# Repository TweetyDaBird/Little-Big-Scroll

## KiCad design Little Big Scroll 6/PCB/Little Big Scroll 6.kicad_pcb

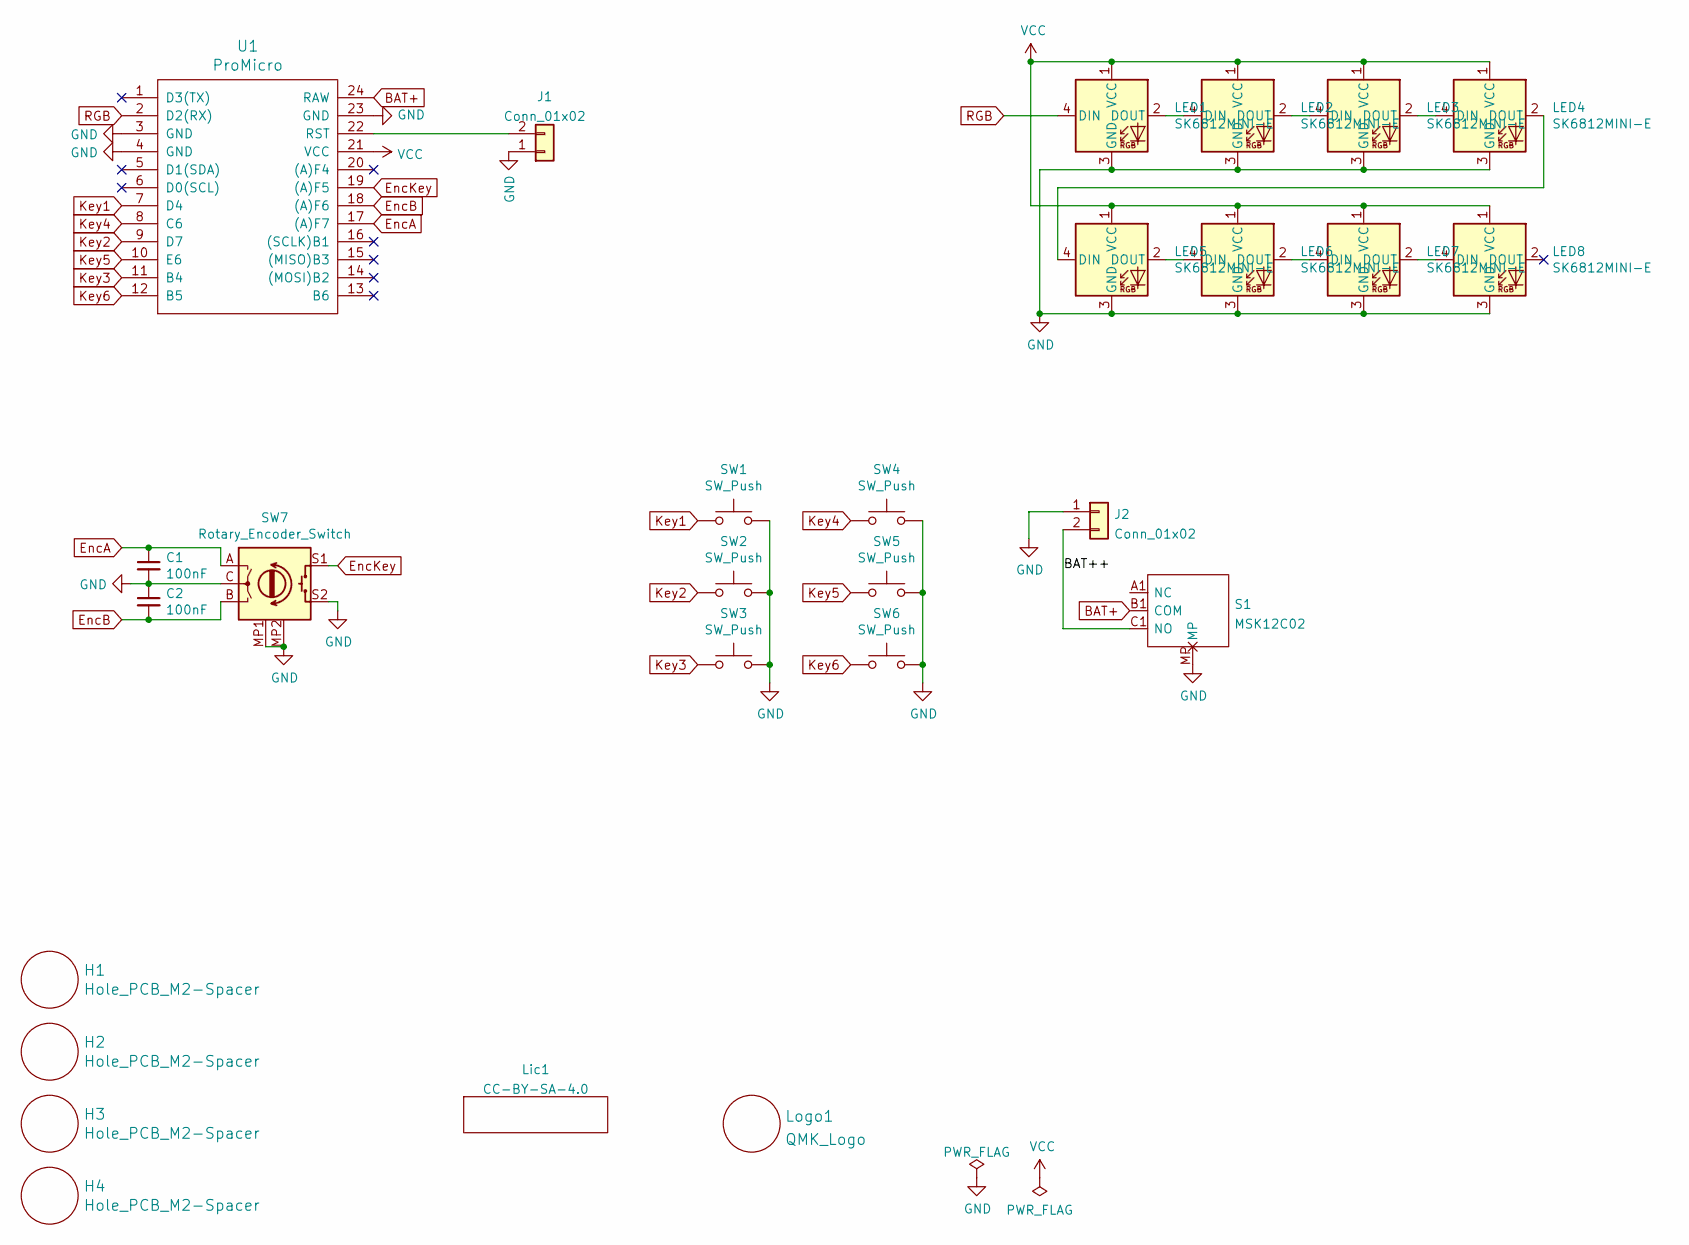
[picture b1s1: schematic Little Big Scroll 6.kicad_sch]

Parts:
C1, C2: 100nF; C_Axial_L3.8mm_D2.6mm_P7.50mm_Horizontal
H1, H2, H3, H4: Hole_PCB_M2-Spacer; MountingHole_3.7mm
J1: Conn_01x02; PinHeader_1x02_P2.54mm_Vertical
J2: Conn_01x02; JST_PH_S2B-PH-K_1x02_P2.00mm_Horizontal
LED1, LED2, LED3, LED4, LED5, LED6, LED7, LED8: SK6812MINI-E; MX_SK6812MINI-E
Lic1: CC-BY-SA-4.0; CC_BY_SA_40
Logo1: QMK_Logo; Powered_by_QMK
S1: MSK12C02; Manufacturer_Part_Number MSK12C02
SW1, SW2, SW3, SW4, SW5, SW6: SW_Push; Kailh_socket_MX_RGB
SW7: Rotary_Encoder_Switch; RotaryEncoder_Alps_EC11E-Switch_Vertical_H20mm
U1: ProMicro; ArduinoProMicro

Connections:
/BAT++: J2.2, S1.C1 (NO)
BAT+: S1.B1 (COM), U1.24 (RAW)
EncA: C1.1, SW7.A, U1.17 ((A)F7)
EncB: C2.2, SW7.B, U1.18 ((A)F6)
EncKey: SW7.S1, U1.19 ((A)F5)
GND: C1.2, C2.1, J1.1, J2.1, LED1.3 (GND), LED2.3 (GND), LED3.3 (GND), LED4.3 (GND), LED5.3 (GND), LED6.3 (GND), LED7.3 (GND), LED8.3 (GND), S1.MP, SW1.1, SW2.1, SW3.1, SW4.1, SW5.1, SW6.1, SW7.C, SW7.MP1 (GND), SW7.MP2 (GND), SW7.S2, U1.3 (GND), U1.4 (GND), U1.23 (GND)
Key1: SW1.2, U1.7 (D4)
Key2: SW2.2, U1.9 (D7)
Key3: SW3.2, U1.11 (B4)
Key4: SW4.2, U1.8 (C6)
Key5: SW5.2, U1.10 (E6)
Key6: SW6.2, U1.12 (B5)
unnamed: J1.2, U1.22 (RST)
unnamed: LED1.2 (DOUT), LED2.4 (DIN)
unnamed: LED2.2 (DOUT), LED3.4 (DIN)
unnamed: LED3.2 (DOUT), LED4.4 (DIN)
unnamed: LED4.2 (DOUT), LED5.4 (DIN)
unnamed: LED5.2 (DOUT), LED6.4 (DIN)
unnamed: LED6.2 (DOUT), LED7.4 (DIN)
unnamed: LED7.2 (DOUT), LED8.4 (DIN)
RGB: LED1.4 (DIN), U1.2 (D2(RX))
VCC: LED1.1 (VCC), LED2.1 (VCC), LED3.1 (VCC), LED4.1 (VCC), LED5.1 (VCC), LED6.1 (VCC), LED7.1 (VCC), LED8.1 (VCC), U1.21 (VCC)

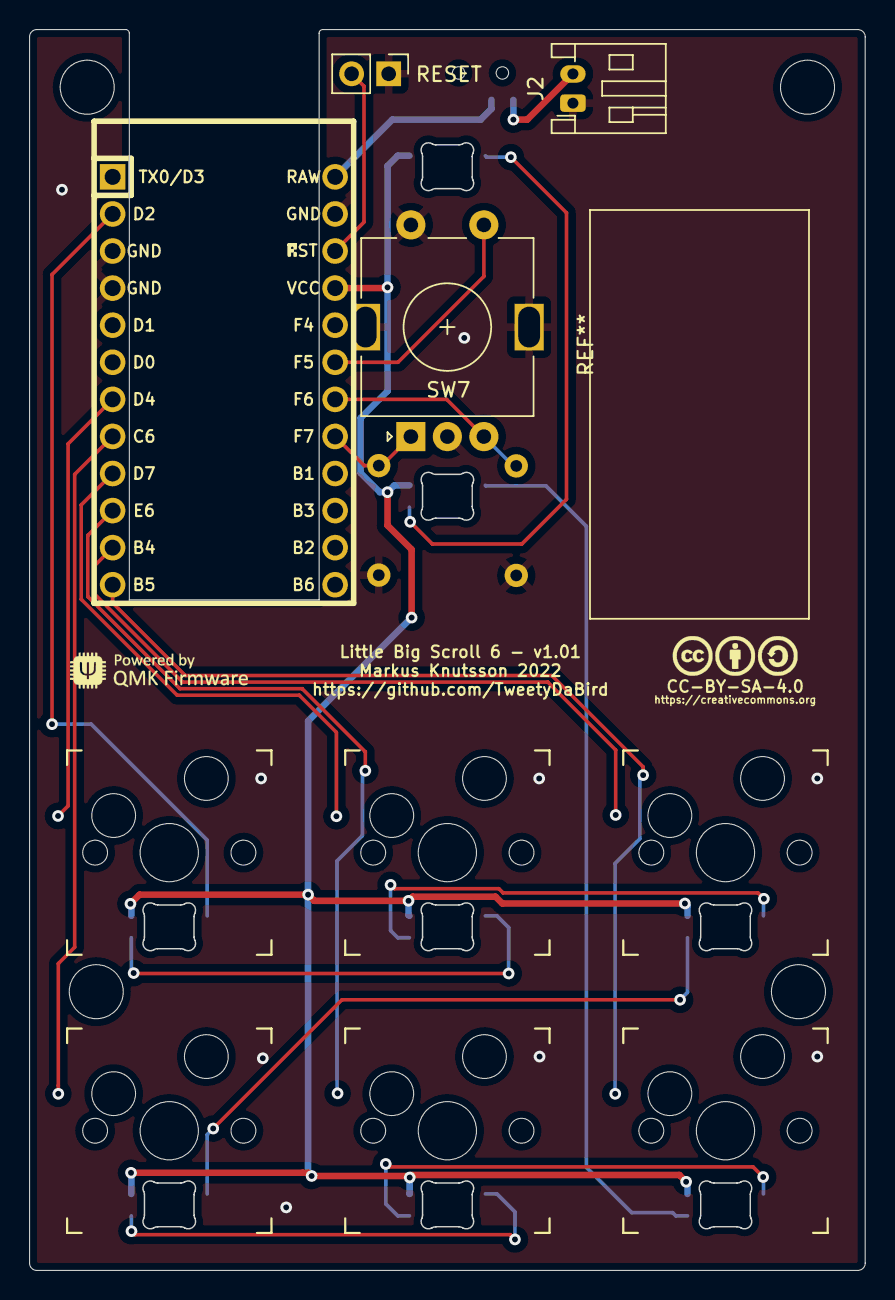
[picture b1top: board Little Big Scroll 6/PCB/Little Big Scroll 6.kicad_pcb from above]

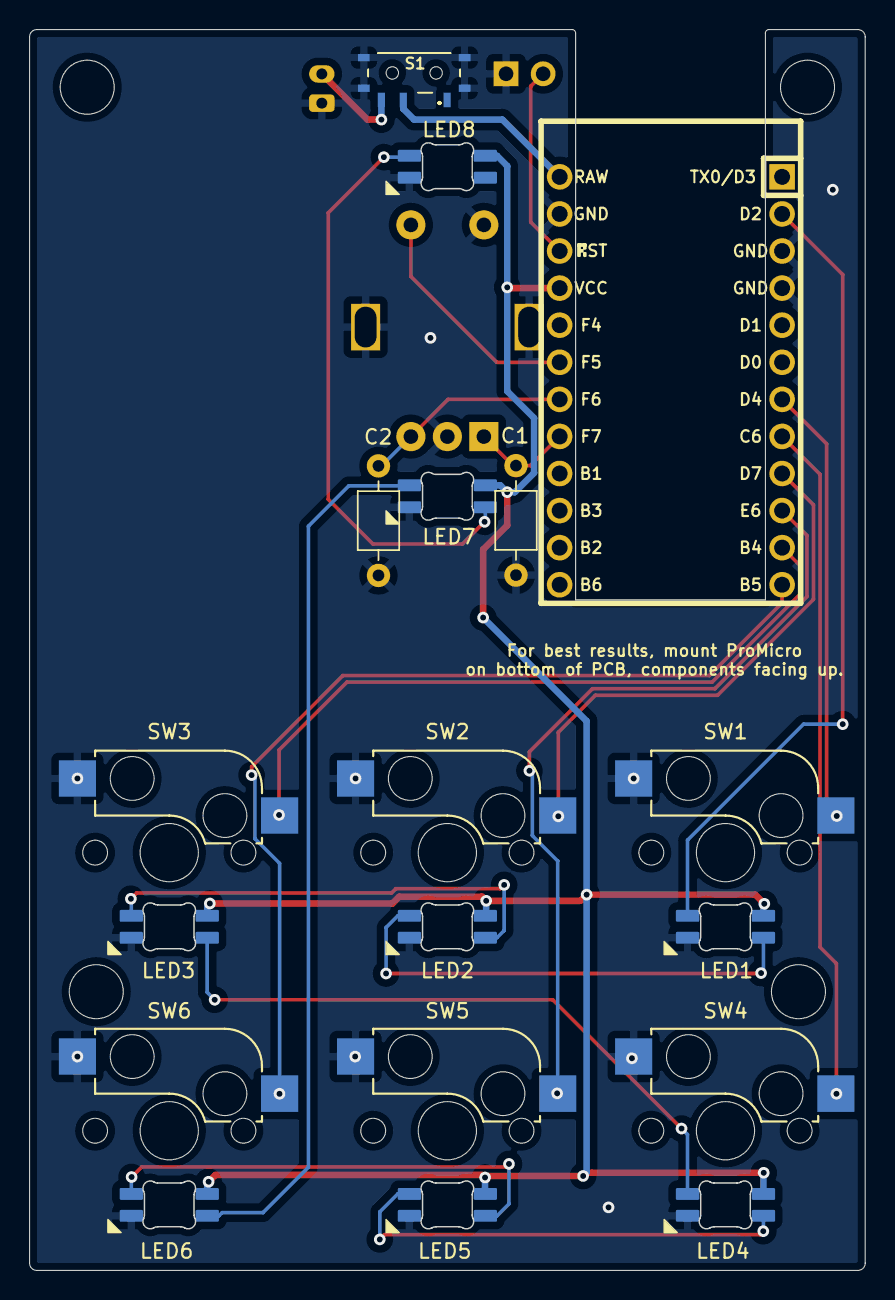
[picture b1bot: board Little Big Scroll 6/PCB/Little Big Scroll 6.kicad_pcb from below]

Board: 2 copper layers, 57.2 x 85.0 mm, 27 parts (3 on the bottom side), 22 nets.

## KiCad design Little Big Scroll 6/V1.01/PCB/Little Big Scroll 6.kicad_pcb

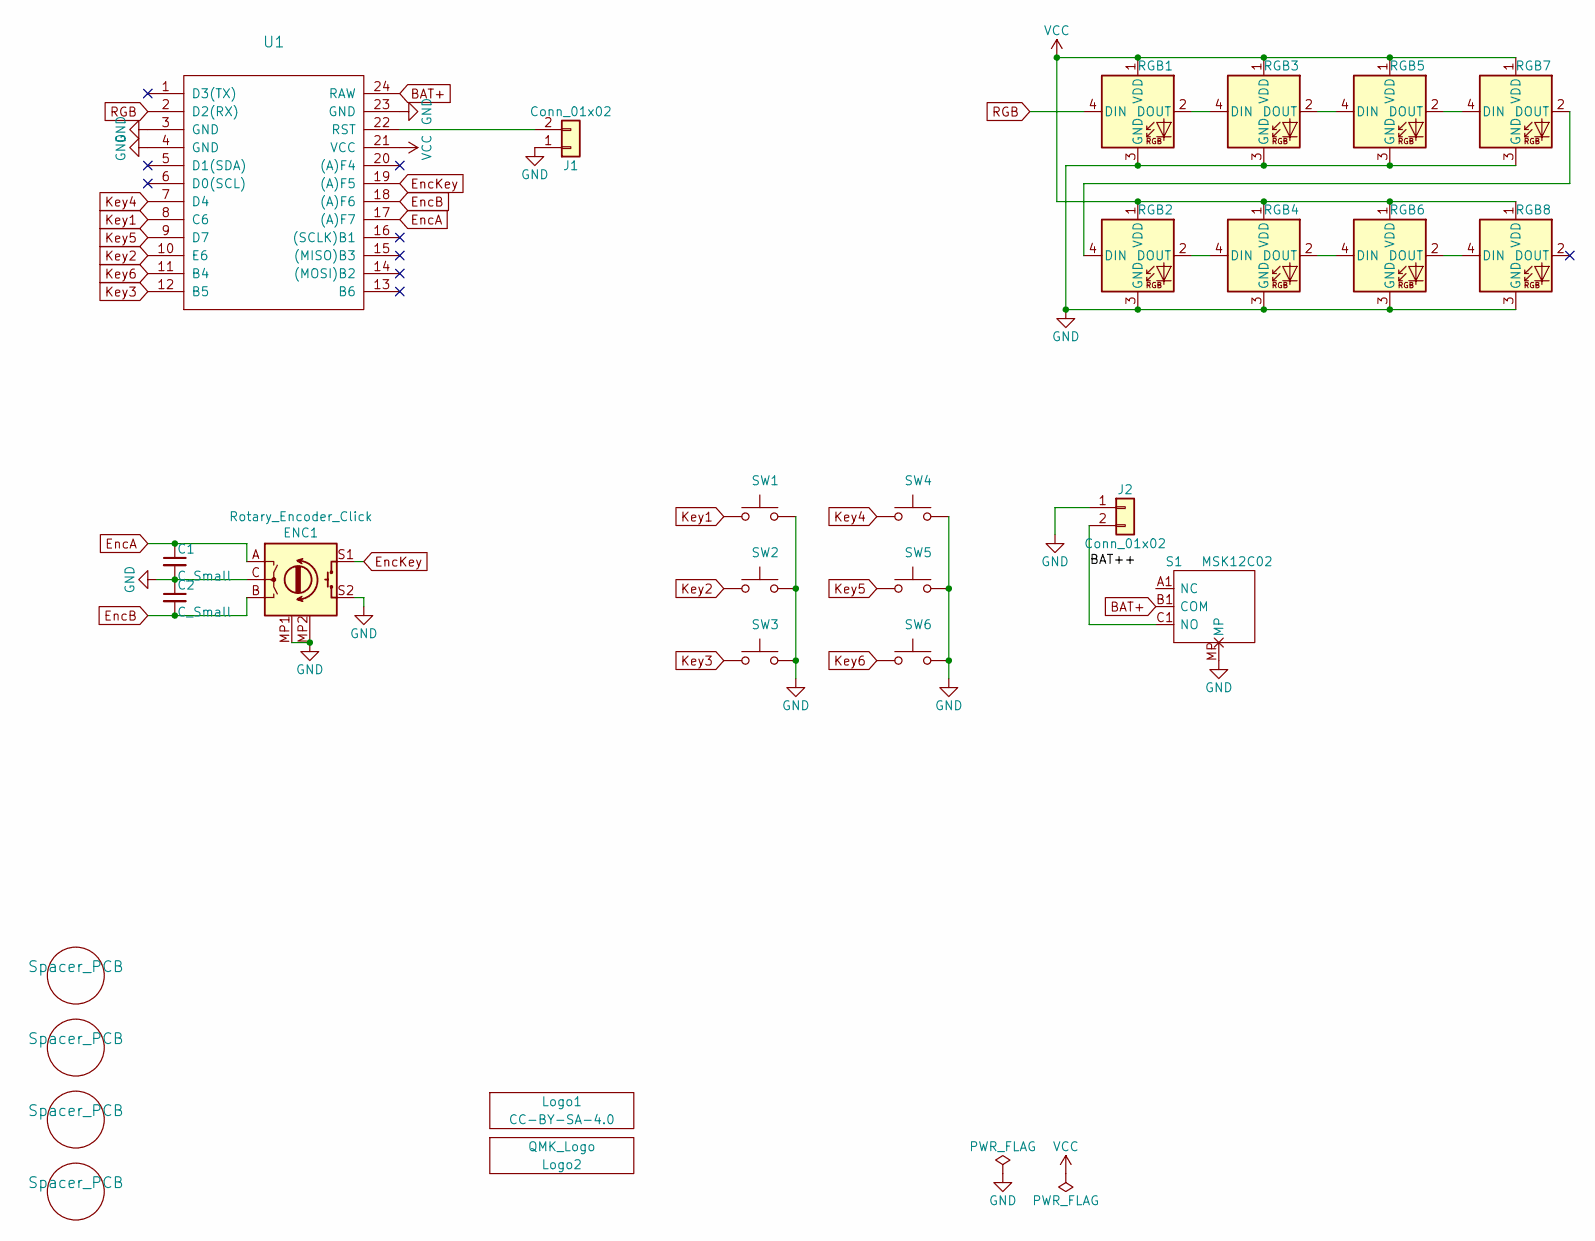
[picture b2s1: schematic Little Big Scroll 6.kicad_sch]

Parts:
C1, C2: C_Small
ENC1: Rotary_Encoder_Click; Encoder_Alps_EC11E
H1, H2, H3, H4: Spacer_PCB; Spacer PCB hole
J1, J2: Conn_01x02
Logo1: CC-BY-SA-4.0; CC_BY_SA_40
Logo2: QMK_Logo; Powered_by_QMK
RGB1, RGB2, RGB3, RGB4, RGB5, RGB6, RGB7, RGB8: SK6812MINI-E; RGB_SK6812MINI-E
S1: MSK12C02; Manufacturer_Part_Number MSK12C02
SW1, SW2, SW3, SW4, SW5, SW6: SW_MX_HS; SW_MX_HotSwap
U1: (no value)

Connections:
/BAT++: J2.2, S1.C1 (NO)
BAT+: S1.B1 (COM), U1.24 (RAW)
EncA: C1.1, ENC1.A, U1.17 ((A)F7)
EncB: C2.2, ENC1.B, U1.18 ((A)F6)
EncKey: ENC1.S1, U1.19 ((A)F5)
GND: C1.2, C2.1, ENC1.C, ENC1.MP1 (GND), ENC1.MP2 (GND), ENC1.S2, J1.1, J2.1, RGB1.3 (GND), RGB2.3 (GND), RGB3.3 (GND), RGB4.3 (GND), RGB5.3 (GND), RGB6.3 (GND), RGB7.3 (GND), RGB8.3 (GND), S1.MP, SW1.2, SW2.2, SW3.2, SW4.2, SW5.2, SW6.2, U1.3 (GND), U1.4 (GND), U1.23 (GND)
Key1: SW1.1, U1.8 (C6)
Key2: SW2.1, U1.10 (E6)
Key3: SW3.1, U1.12 (B5)
Key4: SW4.1, U1.7 (D4)
Key5: SW5.1, U1.9 (D7)
Key6: SW6.1, U1.11 (B4)
unnamed: RGB1.2 (DOUT), RGB3.4 (DIN)
unnamed: RGB2.2 (DOUT), RGB4.4 (DIN)
unnamed: RGB2.4 (DIN), RGB7.2 (DOUT)
unnamed: RGB3.2 (DOUT), RGB5.4 (DIN)
unnamed: RGB4.2 (DOUT), RGB6.4 (DIN)
unnamed: RGB5.2 (DOUT), RGB7.4 (DIN)
unnamed: RGB6.2 (DOUT), RGB8.4 (DIN)
unnamed: J1.2, U1.22 (RST)
RGB: RGB1.4 (DIN), U1.2 (D2(RX))
VCC: RGB1.1 (VDD), RGB2.1 (VDD), RGB3.1 (VDD), RGB4.1 (VDD), RGB5.1 (VDD), RGB6.1 (VDD), RGB7.1 (VDD), RGB8.1 (VDD), U1.21 (VCC)

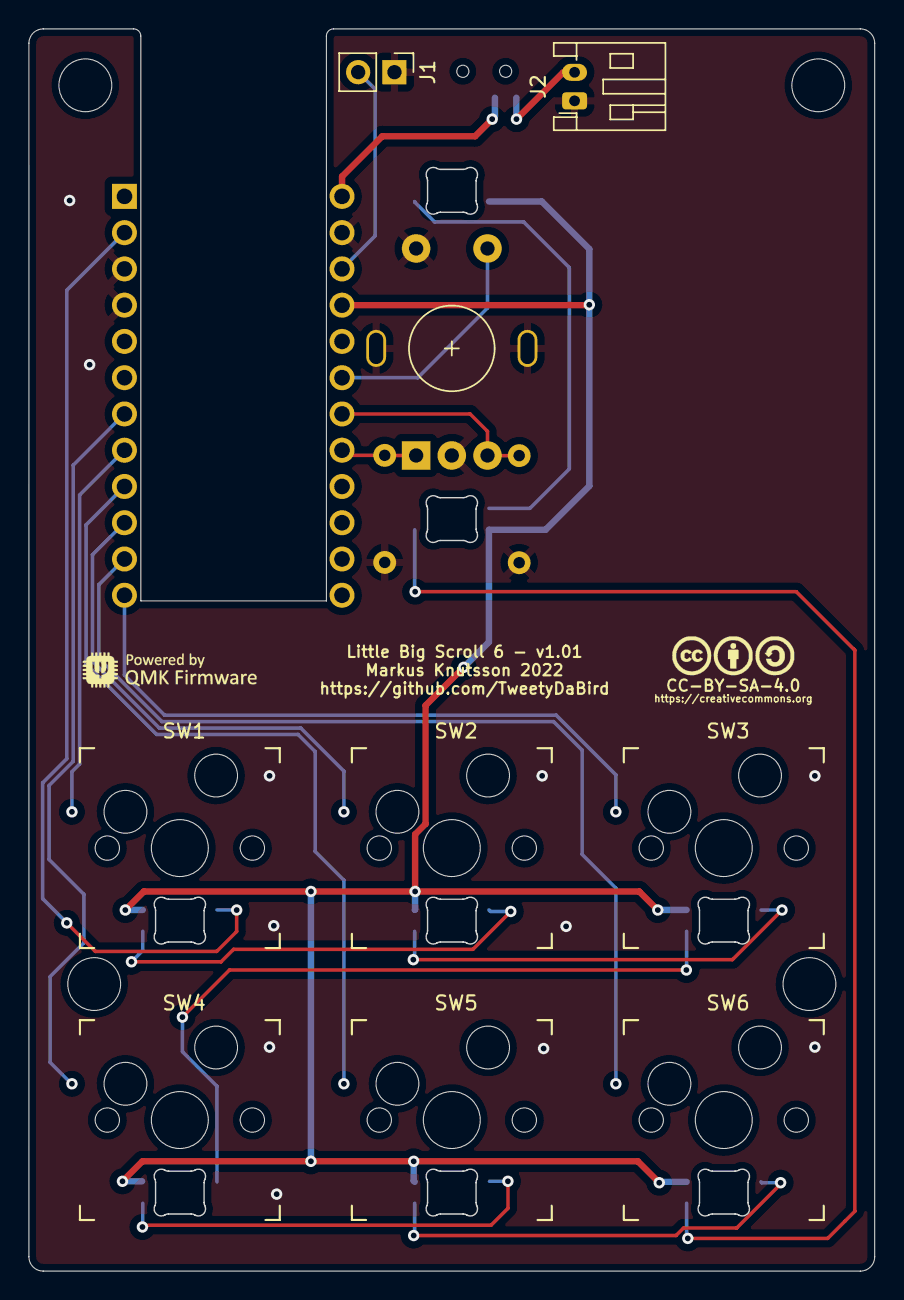
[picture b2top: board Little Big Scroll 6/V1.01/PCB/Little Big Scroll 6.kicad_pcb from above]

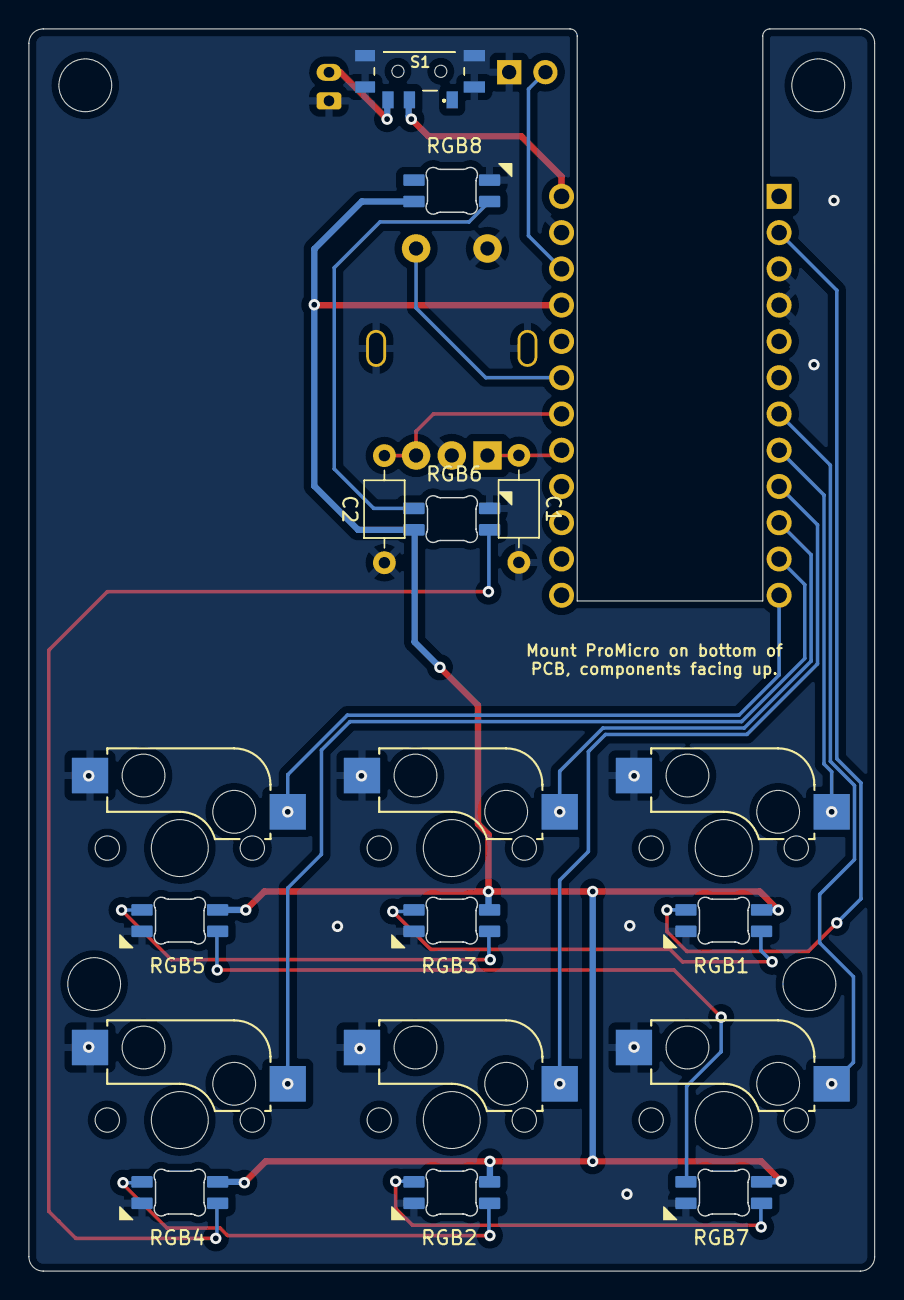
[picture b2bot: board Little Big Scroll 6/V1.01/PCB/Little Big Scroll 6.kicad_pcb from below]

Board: 2 copper layers, 59.2 x 87.0 mm, 27 parts (3 on the bottom side), 22 nets.

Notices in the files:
Little Big Scroll 6/PCB/Little Big Scroll 6.kicad_pcb:
Licensed under Creative Commons BY-SA 4.0 International
